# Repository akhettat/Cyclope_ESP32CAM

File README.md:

# Cyclope_ESP32CAM
Repository that contain the PlatformIO project related to ESP32CAM modules management

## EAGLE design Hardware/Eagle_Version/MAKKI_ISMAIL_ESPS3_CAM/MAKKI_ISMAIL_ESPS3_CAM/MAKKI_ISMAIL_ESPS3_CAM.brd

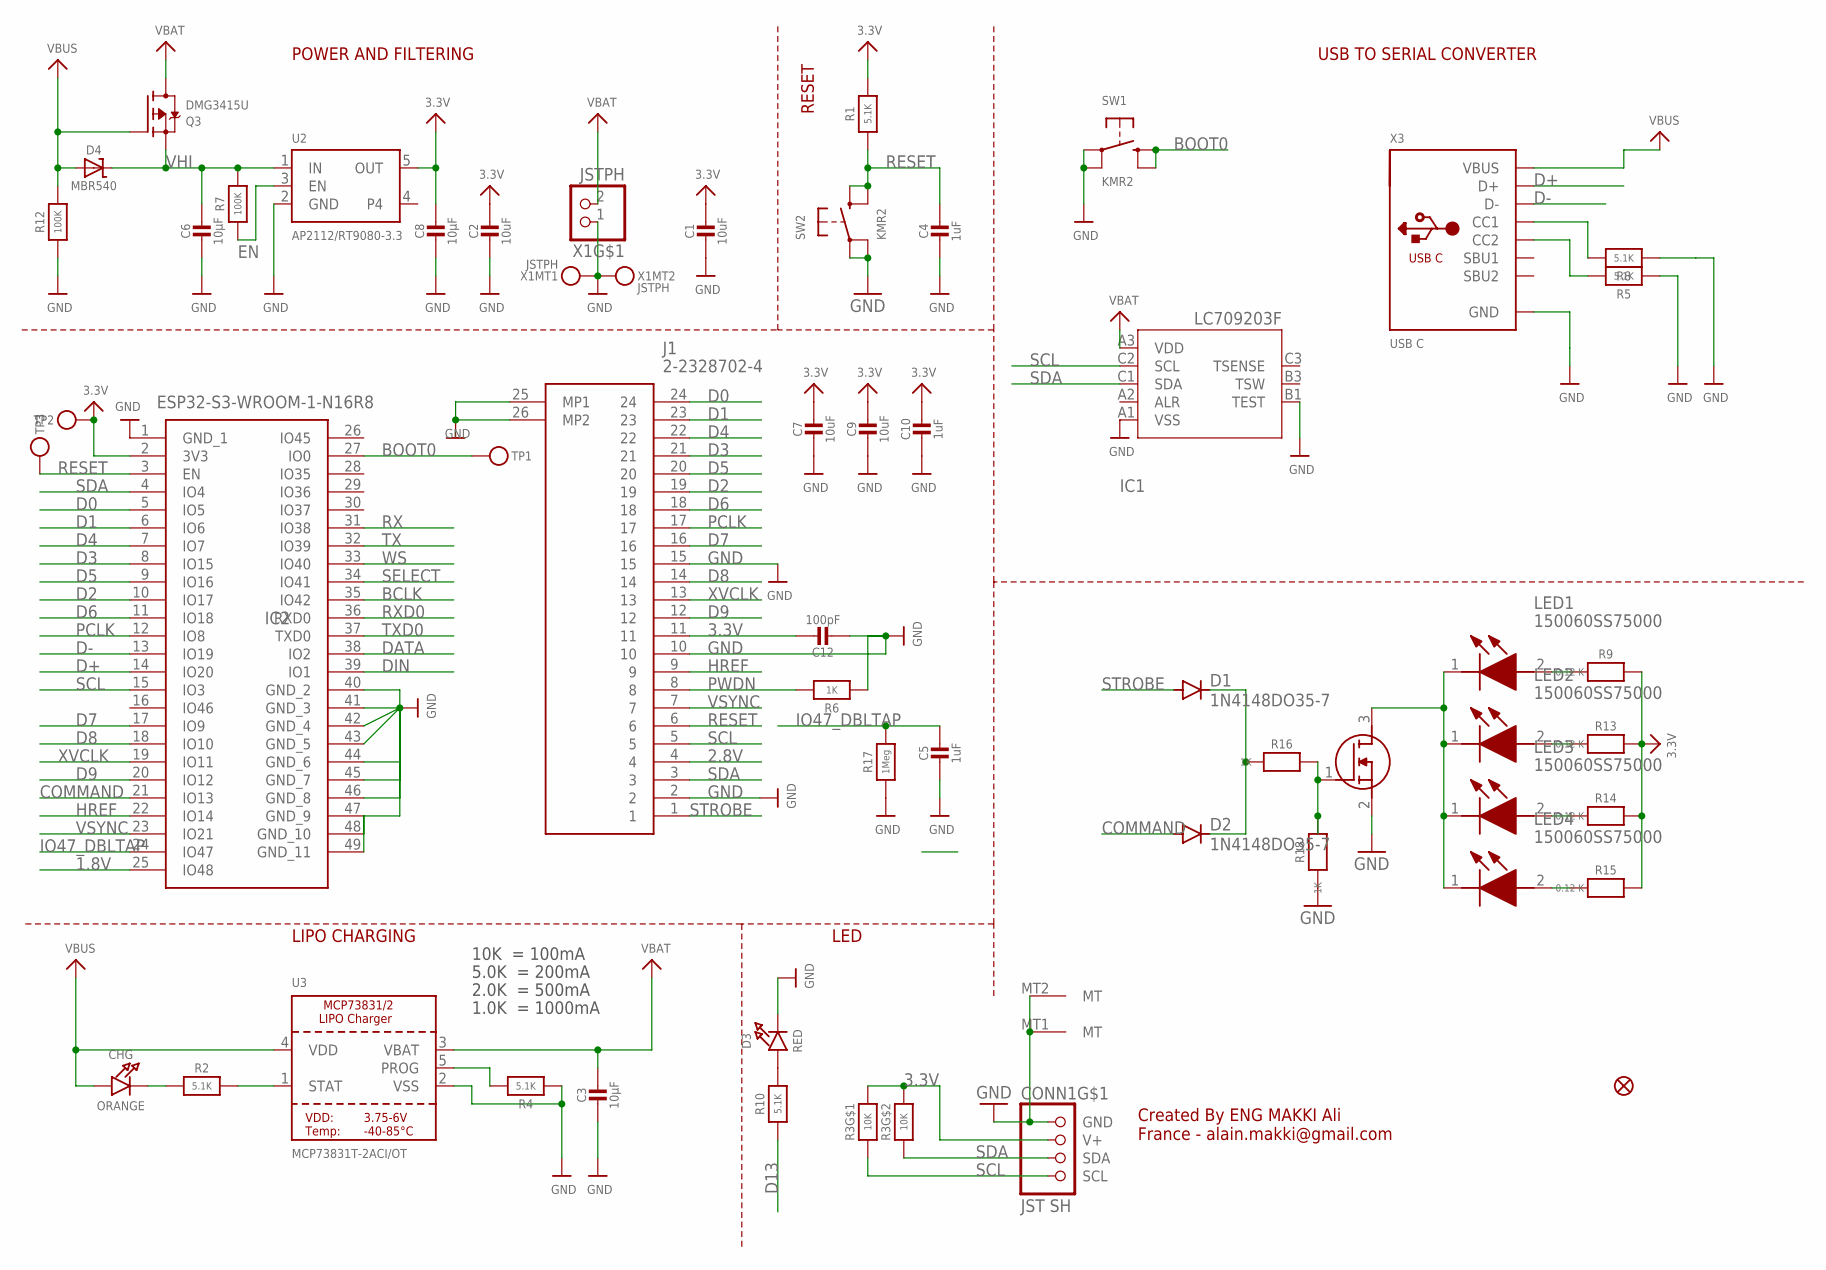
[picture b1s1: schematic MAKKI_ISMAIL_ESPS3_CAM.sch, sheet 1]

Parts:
C1, C2, C7, C9: 10uF; 0805-NO
C3, C6, C8: 10µF; 0805-NO
C4, C5, C10: 1uF; 0603-NO
C12: 100pF; 0805-NO
CHG: ORANGE; CHIPLED_0603_NOOUTLINE
CONN1: JST SH; JST_SH4_RA
D1, D2: 1N4148DO35-7; DO35-7
D3: RED; CHIPLED_0603_NOOUTLINE
D4: MBR540; SOD-123
IC1: LC709203F/MH; WLCSP9
IC2: ESP32-S3-WROOM-1-N16R8; ESP32S3WROOM1N16R8
J1: 2-2328702-4; 223287024
LED1, LED2, LED3, LED4: 150060SS75000; LEDC1608X80N
Q2: 2N7002; SOT96P240X120-3N
Q3: DMG3415U; SOT23-R
R1, R2, R4, R5, R8, R10: 5.1K; 0603-NO
R3: 10K; RESPACK_4X0603
R6, R16, R18: 1K; 0603-NO
R7, R12: 100K; 0603-NO
R9, R13, R14, R15: 0.12 K; 0603-NO
R17: 1Meg; 0603-NO
SW1, SW2: KMR2; BTN_KMR2_4.6X2.8
TP1, TP2, TP3: TESTPOINTROUND1.5MMNO; TESTPOINT_ROUND_1.5MM_NO
U2: AP2112/RT9080-3.3; SOT23-5
U3: MCP73831T-2ACI/OT; SOT23-5
U$34: FIDUCIAL_1MM
X1: JSTPH; JSTPH2_BATT
X3: USB C; USB_C_CUSB31-CFM2AX-01-X

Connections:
1.8V: IC2.25 (IO48)
2.8V: J1.4; also elsewhere on the board
3.3V: C1.1, C2.1, C7.1, C8.1, C9.1, C10.1, C12.1, CONN1.2 (V+), IC2.2 (3V3), J1.11, R1.2, R3.7 (2), R3.8 (2), R9.2, R13.2, R14.2, R15.2, TP2.P$1, U2.5 (OUT); also elsewhere on the board
BCLK: IC2.35 (IO42); also elsewhere on the board
BOOT0: IC2.27 (IO0), SW1.B (S), SW1.B' (S1), TP1.P$1
COMMAND: D2.A, IC2.21 (IO13)
D0: IC2.5 (IO5), J1.24
D1: IC2.6 (IO6), J1.23
D2: IC2.10 (IO17), J1.19
D3: IC2.8 (IO15), J1.21
D4: IC2.7 (IO7), J1.22
D5: IC2.9 (IO16), J1.20
D6: IC2.11 (IO18), J1.18
D7: IC2.17 (IO9), J1.16
D8: IC2.18 (IO10), J1.14
D9: IC2.20 (IO12), J1.12
D13: R10.1
D+: IC2.14 (IO20), X3.A6 (D+), X3.B6 (D+)
D-: IC2.13 (IO19), X3.A7 (D-), X3.B7 (D-)
DATA: IC2.38 (IO2); also elsewhere on the board
DIN: IC2.39 (IO1); also elsewhere on the board
EN: R7.1, U2.3 (EN)
GND: C1.2, C2.2, C3.2, C4.2, C5.2, C6.2, C7.2, C8.2, C9.2, C10.2, C12.2, CONN1.1 (GND), CONN1.MT1 (MT), CONN1.MT2 (MT), D3.C, IC1.A1 (VSS), IC1.B1 (TEST), IC2.1 (GND_1), IC2.40 (GND_2), IC2.41 (GND_3), IC2.42 (GND_4), IC2.43 (GND_5), IC2.44 (GND_6), IC2.45 (GND_7), IC2.46 (GND_8), IC2.47 (GND_9), IC2.48 (GND_10), IC2.49 (GND_11), J1.2, J1.10, J1.15, J1.25 (MP1), J1.26 (MP2), Q2.2 (S), R4.1, R5.1, R6.1, R8.1, R12.1, R17.1, R18.1, SW1.A, SW1.A' (P1), SW2.A, SW2.A' (P1), U2.2 (GND), U3.2 (VSS), X1.1, X1.NC1, X1.NC2, X3.A1B12 (GND), X3.B1A12 (GND); also elsewhere on the board
HREF: IC2.22 (IO14), J1.9
IO47_DBLTAP: C5.1, IC2.24 (IO47), R17.2
unnamed: CHG.C, R2.1
unnamed: LED1.2 (A), R9.1
unnamed: R2.2, U3.1 (STAT)
unnamed: R4.2, U3.5 (PROG)
unnamed: D3.A, R10.2
unnamed: R8.2, X3.A5 (CC1)
unnamed: R5.2, X3.B5 (CC2)
unnamed: LED2.2 (A), R13.1
unnamed: LED3.2 (A), R14.1
unnamed: LED4.2 (A), R15.1
unnamed: LED1.1 (K), LED2.1 (K), LED3.1 (K), LED4.1 (K), Q2.3 (D)
unnamed: D1.C, D2.C, R16.1
unnamed: Q2.1 (G), R16.2, R18.2
PCLK: IC2.12 (IO8), J1.17
PWDN: J1.8, R6.2
RESET: C4.1, IC2.3 (EN), J1.6, R1.1, SW2.B (S), SW2.B' (S1), TP3.P$1
RX: IC2.31 (IO38); also elsewhere on the board
RXD0: IC2.36 (RXD0); also elsewhere on the board
SCL: CONN1.4 (SCL), IC1.C2 (SCL), IC2.15 (IO3), J1.5, R3.1
SDA: CONN1.3 (SDA), IC1.C1 (SDA), IC2.4 (IO4), J1.3, R3.2 (1)
SELECT: IC2.34 (IO41); also elsewhere on the board
STROBE: D1.A, J1.1
TX: IC2.32 (IO39); also elsewhere on the board
TXD0: IC2.37 (TXD0); also elsewhere on the board
VBAT: C3.1, IC1.A3 (VDD), Q3.3 (D), U3.3 (VBAT), X1.2
VBUS: CHG.A, D4.A, Q3.1 (G), R12.2, U3.4 (VDD), X3.A4B9 (VBUS), X3.B4A9 (VBUS)
VHI: C6.1, D4.C, Q3.2 (S), R7.2, U2.1 (IN)
VSYNC: IC2.23 (IO21), J1.7
WS: IC2.33 (IO40); also elsewhere on the board
XVCLK: IC2.19 (IO11), J1.13

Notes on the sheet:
POWER AND FILTERING
RESET
10K = 100mA
5.0K = 200mA
2.0K = 500mA
1.0K = 1000mA
USB TO SERIAL CONVERTER
LIPO CHARGING
LED
Created By ENG MAKKI Ali France - alain.makki@gmail.com

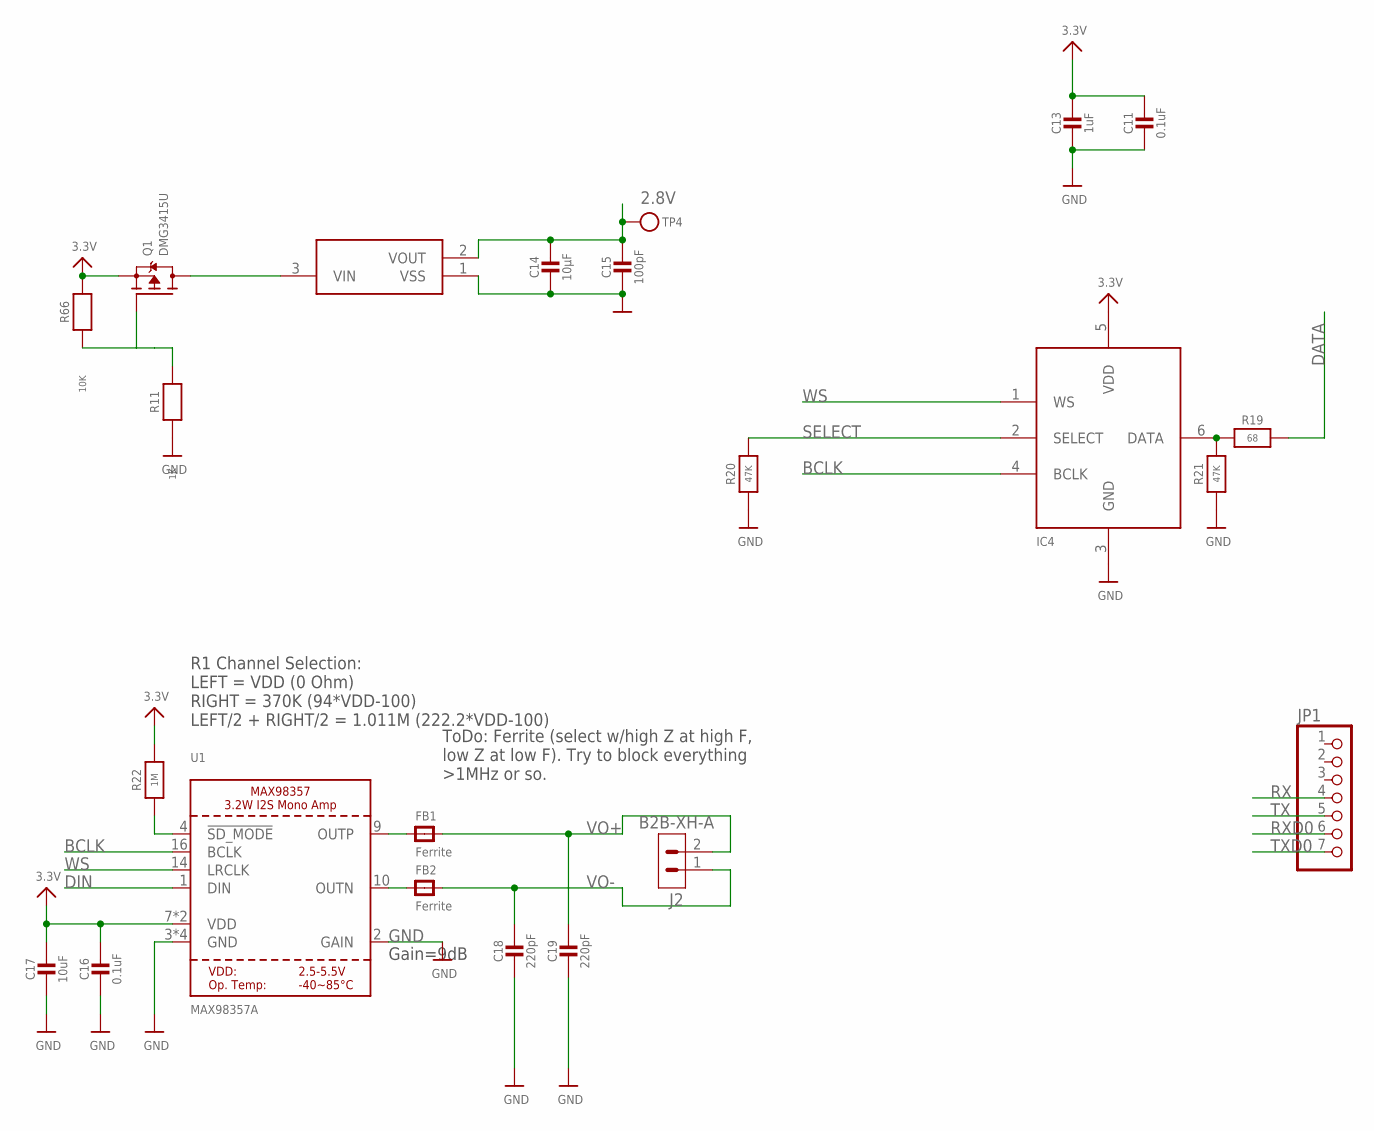
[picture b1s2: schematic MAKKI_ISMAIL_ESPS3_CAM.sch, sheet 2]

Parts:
C11: 0.1uF; 0603-NO
C13: 1uF; 0603-NO
C14: 10µF; 0805-NO
C15: 100pF; 0805-NO
C16: 0.1uF; 0805-NO
C17: 10uF; 0805-NO
C18, C19: 220pF; 0805-NO
FB1, FB2: Ferrite; 0805-NO
IC3: XC6206P282MR-G; SOT95P280X130-3N
IC4: ICS-43434; SPH0645LM4H
J2: B2B-XH-A
JP1: HEADER-1X7THICKER; 1X07_ROUND_76
Q1: DMG3415U; SOT23-R
R11: 1K; 0603-NO
R19: 68; 0603-NO
R20, R21: 47K; 0603-NO
R22: 1M; 0805-NO
R66: 10K; 0603-NO
TP4: TESTPOINTROUND1.5MMNO; TESTPOINT_ROUND_1.5MM_NO
U1: MAX98357A; QFN16_3MM

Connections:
2.8V: C14.1, C15.1, IC3.2 (VOUT), TP4.P$1; also elsewhere on the board
3.3V: C11.1, C13.1, C16.1, C17.1, IC4.5 (VDD), Q1.2 (S), R22.2, R66.2, U1.7 (VDD), U1.8 (VDD); also elsewhere on the board
BCLK: IC4.4 (BCLK), U1.16 (BCLK); also elsewhere on the board
DATA: R19.2; also elsewhere on the board
DIN: U1.1 (DIN); also elsewhere on the board
GND: C11.2, C13.2, C14.2, C15.2, C16.2, C17.2, C18.2, C19.2, IC3.1 (VSS), IC4.3 (GND), R11.1, R20.1, R21.1, U1.2 (GAIN), U1.3 (GND), U1.11 (GND), U1.15 (GND), U1.THERMAL (GND); also elsewhere on the board
unnamed: Q1.1 (G), R11.2, R66.1
unnamed: IC3.3 (VIN), Q1.3 (D)
unnamed: IC4.6 (DATA), R19.1, R21.2
unnamed: FB2.1, U1.10 (OUTN)
unnamed: FB1.1, U1.9 (OUTP)
RX: JP1.4; also elsewhere on the board
RXD0: JP1.6; also elsewhere on the board
SD_MODE: R22.1, U1.4 (!SD_MODE)
SELECT: IC4.2 (SELECT), R20.2; also elsewhere on the board
TX: JP1.5; also elsewhere on the board
TXD0: JP1.7; also elsewhere on the board
VO+: C19.1, FB1.2, J2.2
VO-: C18.1, FB2.2, J2.1
WS: IC4.1 (WS), U1.14 (LRCLK); also elsewhere on the board

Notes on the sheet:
R1 Channel Selection: LEFT = VDD (0 Ohm) RIGHT = 370K (94*VDD-100) LEFT/2 + RIGHT/2 = 1.011M (222.2*VDD-100)
ToDo: Ferrite (select w/high Z at high F, low Z at low F). Try to block everything >1MHz or so.
Gain=9dB

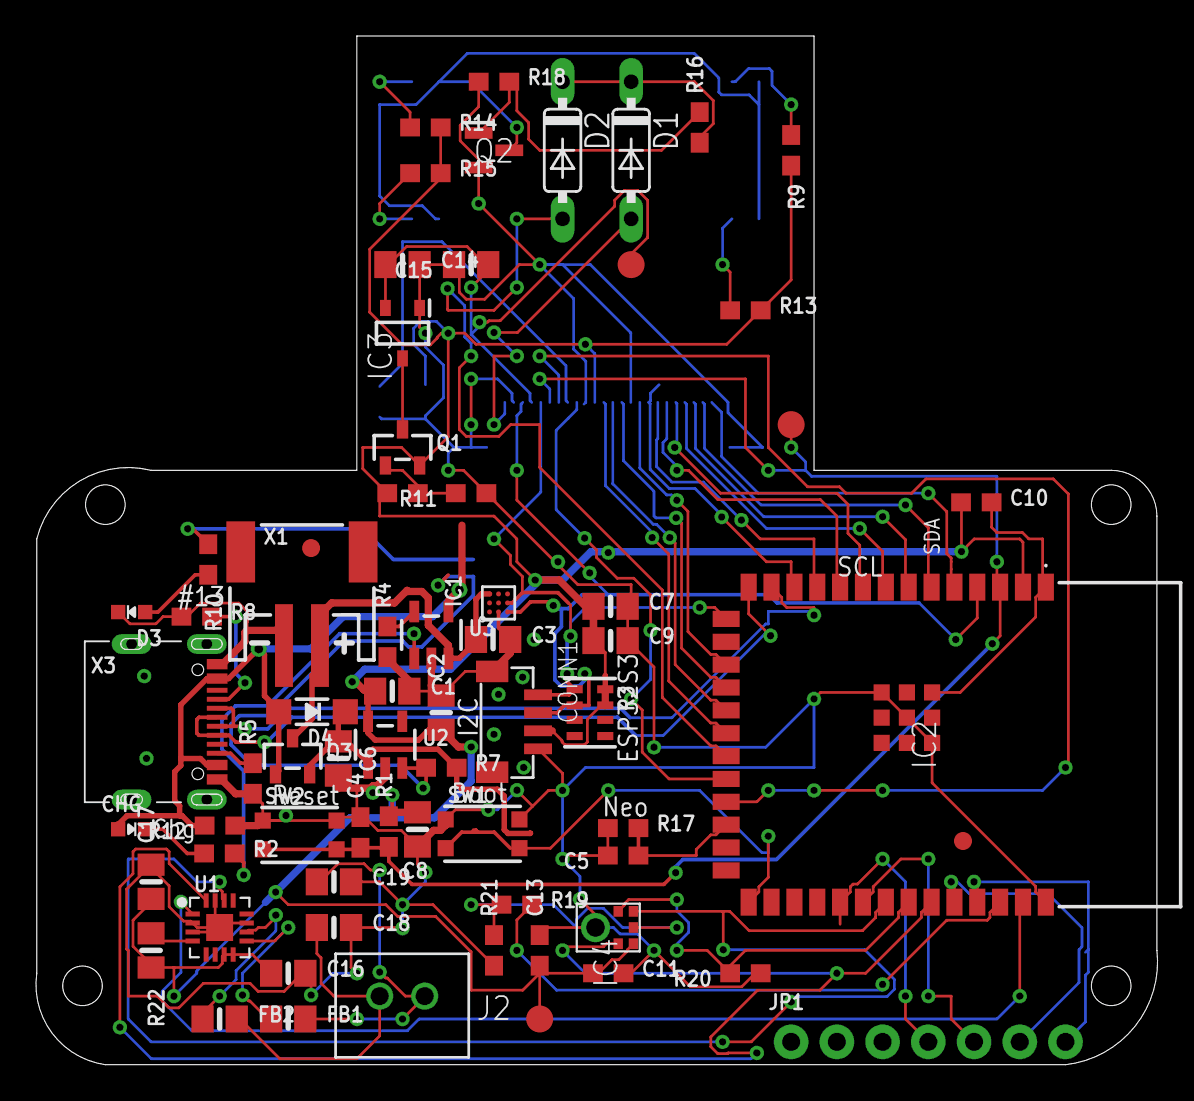
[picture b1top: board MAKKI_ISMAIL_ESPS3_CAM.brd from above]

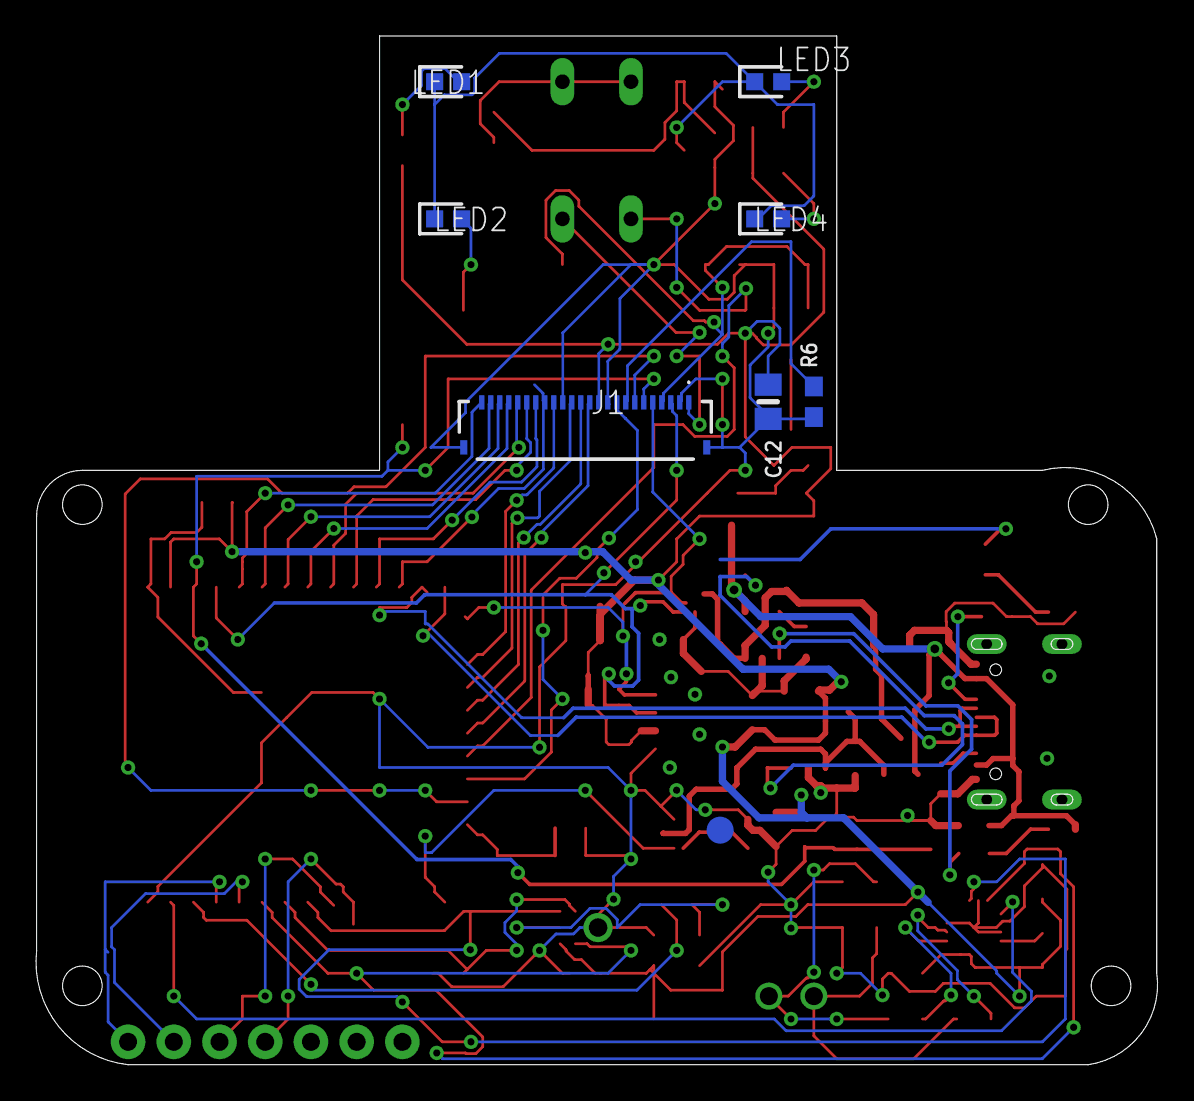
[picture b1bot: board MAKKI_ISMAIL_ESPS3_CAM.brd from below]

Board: 2 copper layers, 62.3 x 57.2 mm, 77 parts (8 on the bottom side), 61 nets.

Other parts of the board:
U$35: FIDUCIAL_1MM

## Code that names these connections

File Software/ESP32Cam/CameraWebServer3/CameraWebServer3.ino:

#include "esp_camera.h"
#include <WiFi.h>
#include <WebServer.h>

#define CAMERA_MODEL_AI_THINKER

#include "camera_pins.h"

const char* ssid = "****"; // Remplacez par votre SSID WiFi
const char* password = "****"; // Remplacez par votre mot de passe WiFi

WebServer server(80);

void handleRoot() {
  server.send(200, "text/plain", "Hello, this is ESP32-CAM");
}

void handleCapture() {
  camera_fb_t * fb = NULL;
  fb = esp_camera_fb_get();
  if (!fb) {
    Serial.println("Camera capture failed");
    server.send(500, "text/plain", "Camera capture failed");
    return;
  }

  Serial.println("Camera capture succeeded");

  WiFiClient client = server.client();

  client.println("HTTP/1.1 200 OK");
  client.println("Content-Type: image/jpeg");
  client.print("Content-Length: ");
  client.println(fb->len);
  client.println();
  client.write(fb->buf, fb->len);

  esp_camera_fb_return(fb);
}

void setup() {
  Serial.begin(115200);
  Serial.setDebugOutput(true);
  Serial.println();

  // Configuration de la caméra
  camera_config_t config;
  config.ledc_channel = LEDC_CHANNEL_0;
  config.ledc_timer = LEDC_TIMER_0;
  config.pin_d0 = Y2_GPIO_NUM;
  config.pin_d1 = Y3_GPIO_NUM;
  config.pin_d2 = Y4_GPIO_NUM;
  config.pin_d3 = Y5_GPIO_NUM;
  config.pin_d4 = Y6_GPIO_NUM;
  config.pin_d5 = Y7_GPIO_NUM;
  config.pin_d6 = Y8_GPIO_NUM;
  config.pin_d7 = Y9_GPIO_NUM;
  config.pin_xclk = XCLK_GPIO_NUM;
  config.pin_pclk = PCLK_GPIO_NUM;
  config.pin_vsync = VSYNC_GPIO_NUM;
  config.pin_href = HREF_GPIO_NUM;
  config.pin_sscb_sda = SIOD_GPIO_NUM;
  config.pin_sscb_scl = SIOC_GPIO_NUM;
  config.pin_pwdn = PWDN_GPIO_NUM;
  config.pin_reset = RESET_GPIO_NUM;
  config.xclk_freq_hz = 20000000;
  config.pixel_format = PIXFORMAT_JPEG;

  if (psramFound()) {
    config.frame_size = FRAMESIZE_SVGA;
    config.jpeg_quality = 2;
    config.fb_count = 2;
  } else {
    config.frame_size = FRAMESIZE_SVGA;
    config.jpeg_quality = 2;
    config.fb_count = 1;
  }

  esp_err_t err = esp_camera_init(&config);
  if (err != ESP_OK) {
    Serial.printf("Camera init failed with error 0x%x", err);
    return;
  }

  WiFi.begin(ssid, password);

  while (WiFi.status() != WL_CONNECTED) {
    delay(500);
    Serial.print(".");
  }
  Serial.println("");
  Serial.println("WiFi connected");

  Serial.print("Camera Ready! Use 'http://");
  Serial.print(WiFi.localIP());
  Serial.println("' to connect");

  server.on("/", HTTP_GET, handleRoot);
  server.on("/capture", HTTP_GET, handleCapture);
  server.begin();
}

void loop() {
  server.handleClient();
}

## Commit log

2024-12-08 CodeESP32/Serveur
2024-12-08 password
2025-02-01 Code qui envoie vidéo en temps réel sur url
2025-10-31 Update file organization
2026-02-07 Glasses3D
2026-02-11 PCB_firmware added
2026-02-11 CameraWebS et Yolo
2026-02-11 3Dimages
2026-02-11 Add Hardware design
2026-02-13 Version Corrige

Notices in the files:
parts and their libraries:
microbuilder: This work is placed in the public domain, and may be freely used for commercial and non-commercial work with the following conditions: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
